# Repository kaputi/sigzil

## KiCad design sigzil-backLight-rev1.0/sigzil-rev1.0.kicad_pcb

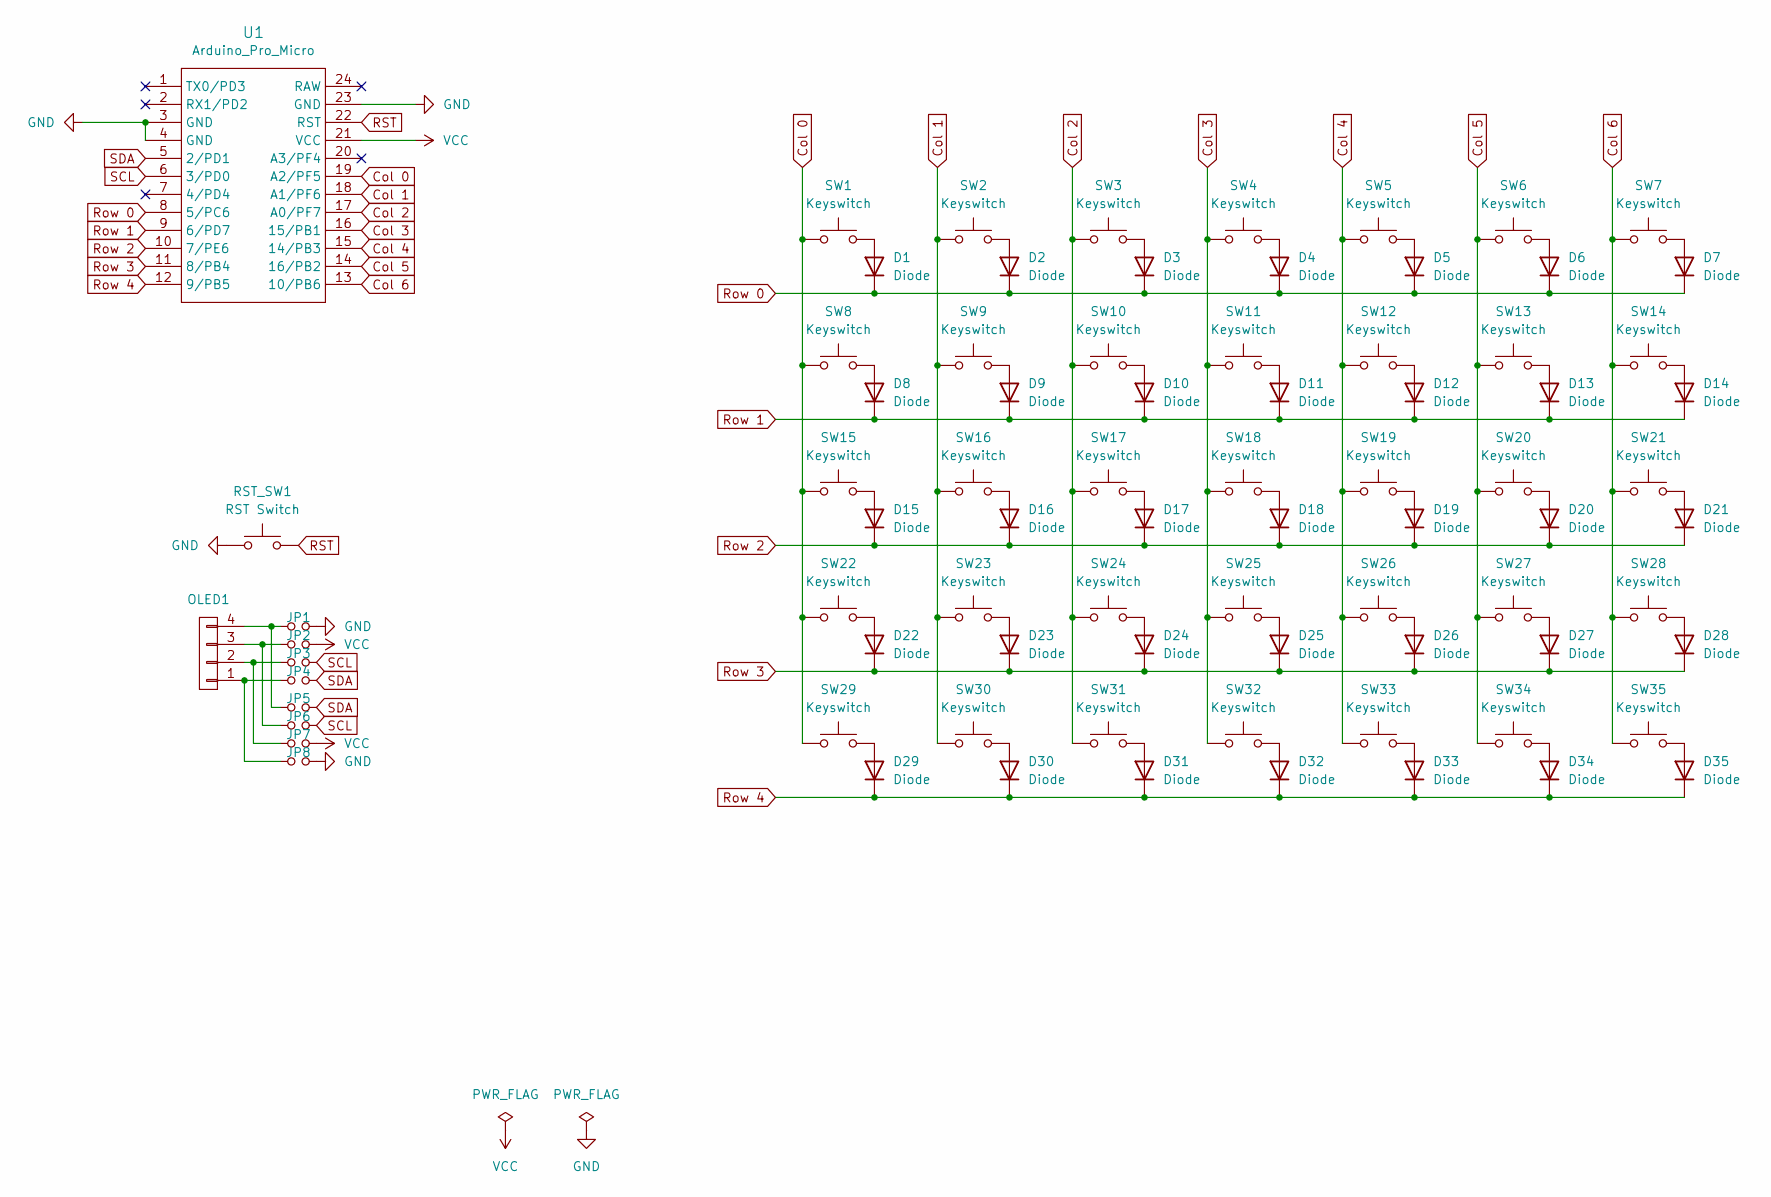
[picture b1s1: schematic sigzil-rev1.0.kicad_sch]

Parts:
D1, D2, D3, D4, D5, D6, D7, D8, D9, D10, D11, D12, D13, D14, D15, D16, D17, D18, D19, D20, D21, D22, D23, D24, D25, D26, D27, D28, D29, D30, D31, D32, D33, D34, D35: Diode; Diode_TH_SOD123
JP1, JP2, JP3, JP4, JP5, JP6, JP7, JP8: Jumper
OLED1: OLED_4Pin
RST_SW1: RST Switch; TACT_SWITCH_TVBP06
SW1, SW8, SW14, SW15, SW22, SW33: Keyswitch; MX_PCB_1.25u
SW2, SW3, SW4, SW5, SW6, SW7, SW9, SW10, SW11, SW12, SW13, SW16, SW17, SW18, SW19, SW20, SW21, SW23, SW24, SW25, SW26, SW27, SW28, SW29, SW30, SW31, SW32: Keyswitch; MX_PCB_1.00u
SW34, SW35: Keyswitch; MX_PCB_1.25u_90deg
U1: Arduino_Pro_Micro; ProMicro

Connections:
Col 0: SW1.1, SW8.1, SW15.1, SW22.1, SW29.1, U1.19 (A2/PF5)
Col 1: SW2.1, SW9.1, SW16.1, SW23.1, SW30.1, U1.18 (A1/PF6)
Col 2: SW3.1, SW10.1, SW17.1, SW24.1, SW31.1, U1.17 (A0/PF7)
Col 3: SW4.1, SW11.1, SW18.1, SW25.1, SW32.1, U1.16 (15/PB1)
Col 4: SW5.1, SW12.1, SW19.1, SW26.1, SW33.1, U1.15 (14/PB3)
Col 5: SW6.1, SW13.1, SW20.1, SW27.1, SW34.1, U1.14 (16/PB2)
Col 6: SW7.1, SW14.1, SW21.1, SW28.1, SW35.1, U1.13 (10/PB6)
GND: JP1.2, JP8.2, RST_SW1.1, U1.3 (GND), U1.4 (GND), U1.23 (GND)
unnamed: D1.2 (A), SW1.2
unnamed: D2.2 (A), SW2.2
unnamed: D3.2 (A), SW3.2
unnamed: D4.2 (A), SW4.2
unnamed: D5.2 (A), SW5.2
unnamed: D6.2 (A), SW6.2
unnamed: D7.2 (A), SW7.2
unnamed: D8.2 (A), SW8.2
unnamed: D9.2 (A), SW9.2
unnamed: D10.2 (A), SW10.2
unnamed: D11.2 (A), SW11.2
unnamed: D12.2 (A), SW12.2
unnamed: D13.2 (A), SW13.2
unnamed: D14.2 (A), SW14.2
unnamed: D15.2 (A), SW15.2
unnamed: D16.2 (A), SW16.2
unnamed: D17.2 (A), SW17.2
unnamed: D18.2 (A), SW18.2
unnamed: D19.2 (A), SW19.2
unnamed: D20.2 (A), SW20.2
unnamed: D21.2 (A), SW21.2
unnamed: D22.2 (A), SW22.2
unnamed: D23.2 (A), SW23.2
unnamed: D24.2 (A), SW24.2
unnamed: D25.2 (A), SW25.2
unnamed: D26.2 (A), SW26.2
unnamed: D27.2 (A), SW27.2
unnamed: D28.2 (A), SW28.2
unnamed: D29.2 (A), SW29.2
unnamed: D30.2 (A), SW30.2
unnamed: D31.2 (A), SW31.2
unnamed: D32.2 (A), SW32.2
unnamed: D33.2 (A), SW33.2
unnamed: D34.2 (A), SW34.2
unnamed: D35.2 (A), SW35.2
unnamed: JP4.1, JP8.1, OLED1.1
unnamed: JP3.1, JP7.1, OLED1.2
unnamed: JP2.1, JP6.1, OLED1.3
unnamed: JP1.1, JP5.1, OLED1.4
RST: RST_SW1.2, U1.22 (RST)
Row 0: D1.1 (K), D2.1 (K), D3.1 (K), D4.1 (K), D5.1 (K), D6.1 (K), D7.1 (K), U1.8 (5/PC6)
Row 1: D8.1 (K), D9.1 (K), D10.1 (K), D11.1 (K), D12.1 (K), D13.1 (K), D14.1 (K), U1.9 (6/PD7)
Row 2: D15.1 (K), D16.1 (K), D17.1 (K), D18.1 (K), D19.1 (K), D20.1 (K), D21.1 (K), U1.10 (7/PE6)
Row 3: D22.1 (K), D23.1 (K), D24.1 (K), D25.1 (K), D26.1 (K), D27.1 (K), D28.1 (K), U1.11 (8/PB4)
Row 4: D29.1 (K), D30.1 (K), D31.1 (K), D32.1 (K), D33.1 (K), D34.1 (K), D35.1 (K), U1.12 (9/PB5)
SCL: JP3.2, JP6.2, U1.6 (3/PD0)
SDA: JP4.2, JP5.2, U1.5 (2/PD1)
VCC: JP2.2, JP7.2, U1.21 (VCC)

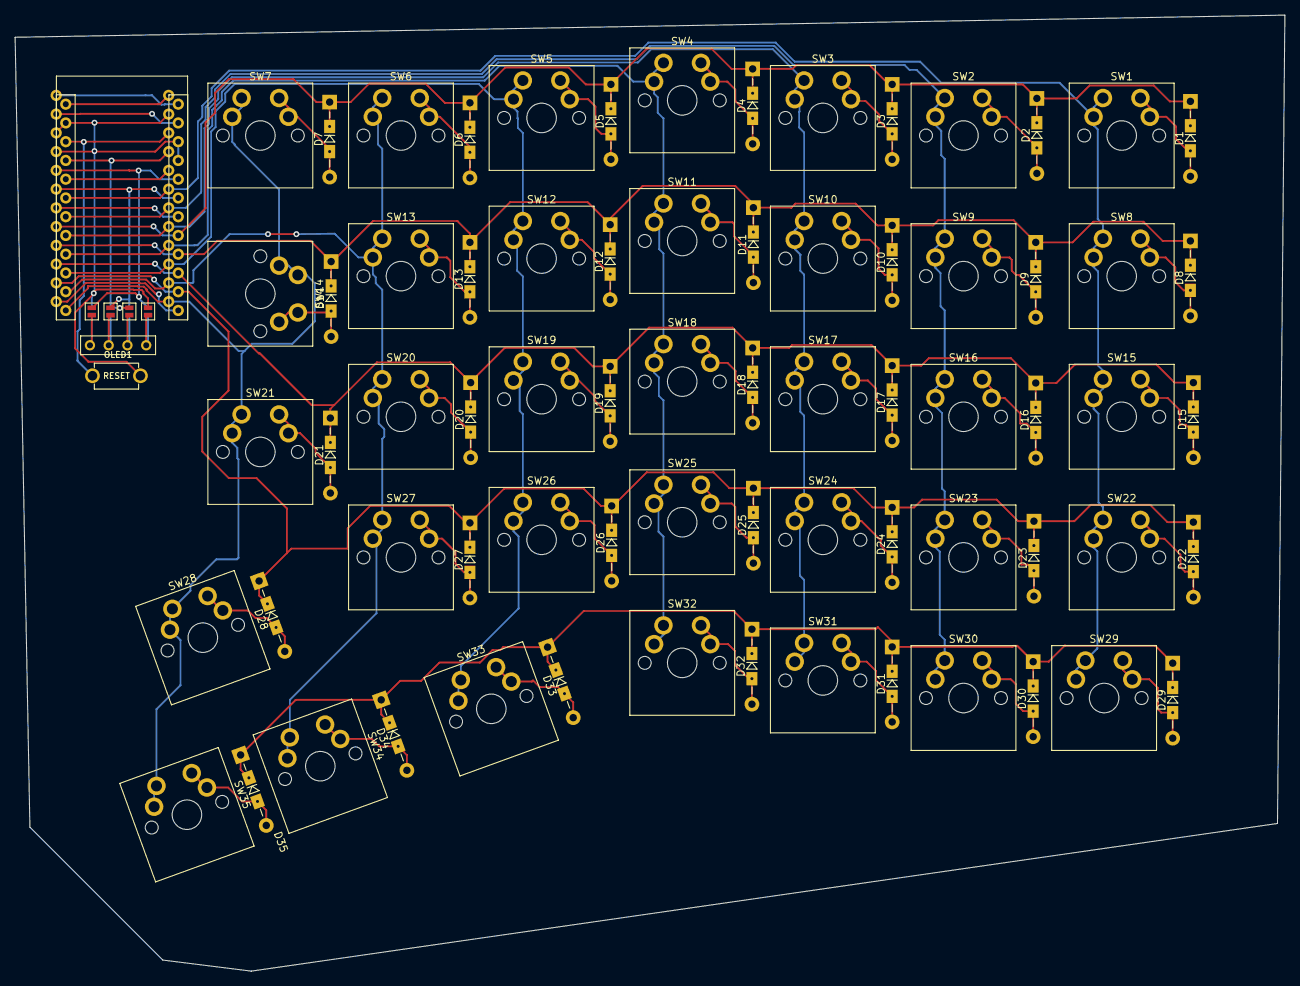
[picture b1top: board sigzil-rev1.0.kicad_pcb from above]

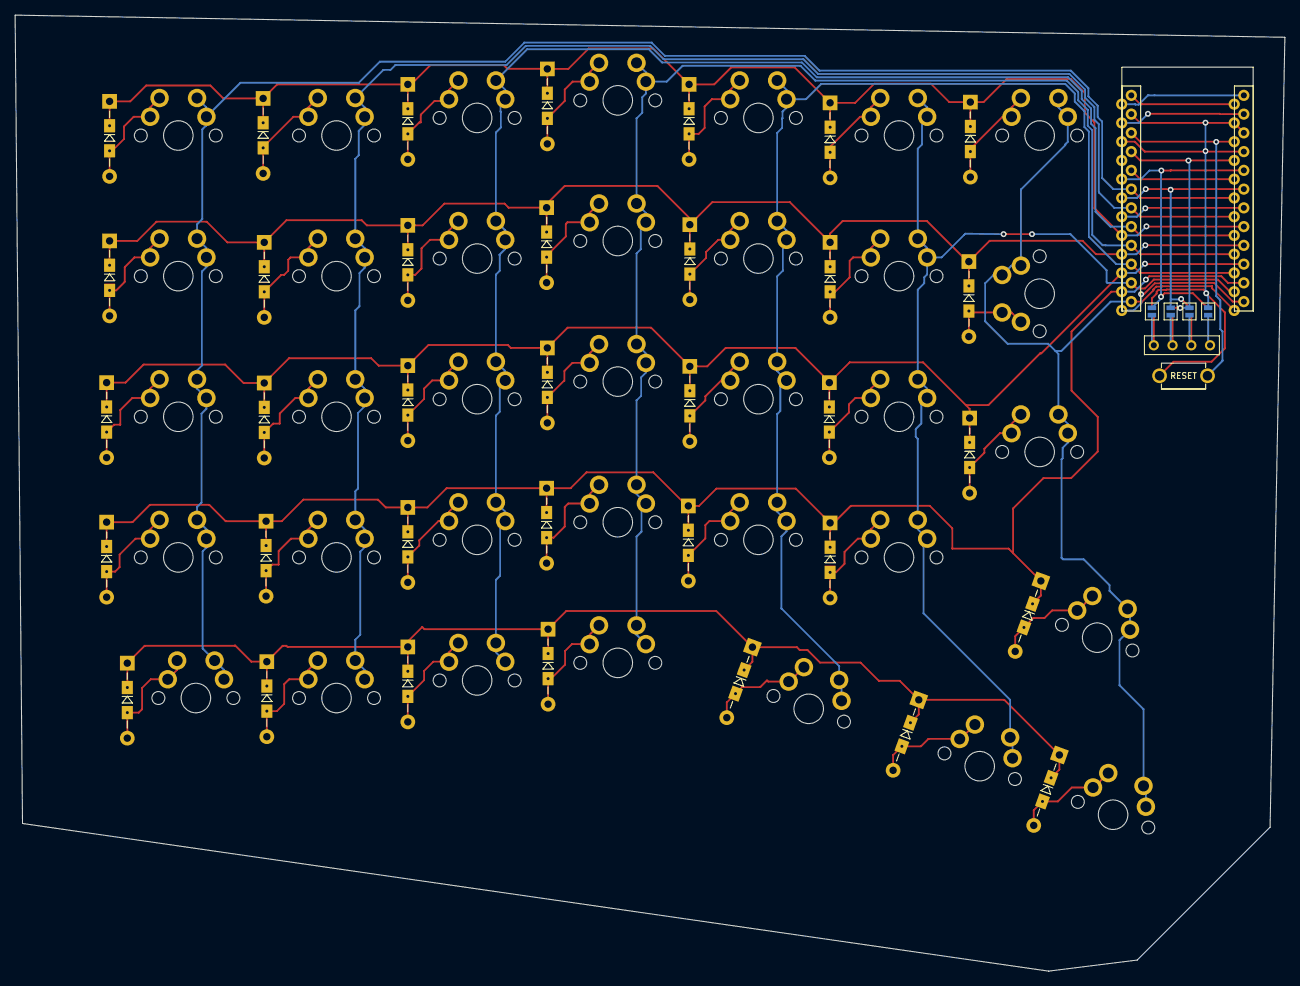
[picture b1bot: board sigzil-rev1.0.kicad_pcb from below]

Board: 2 copper layers, 172.0 x 129.5 mm, 81 parts (4 on the bottom side), 56 nets.

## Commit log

2023-12-28 WIP WIP
